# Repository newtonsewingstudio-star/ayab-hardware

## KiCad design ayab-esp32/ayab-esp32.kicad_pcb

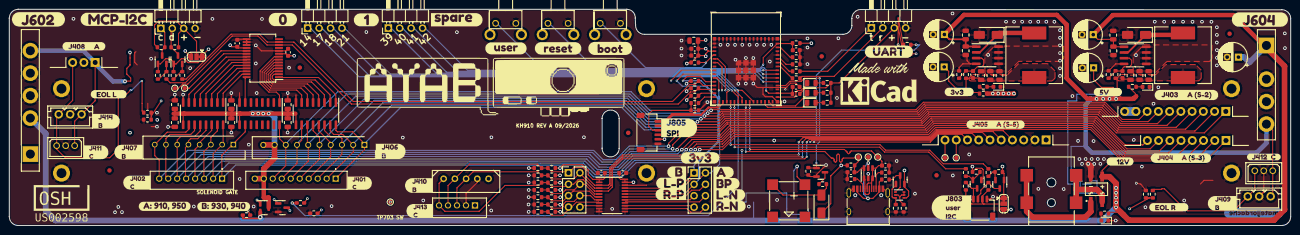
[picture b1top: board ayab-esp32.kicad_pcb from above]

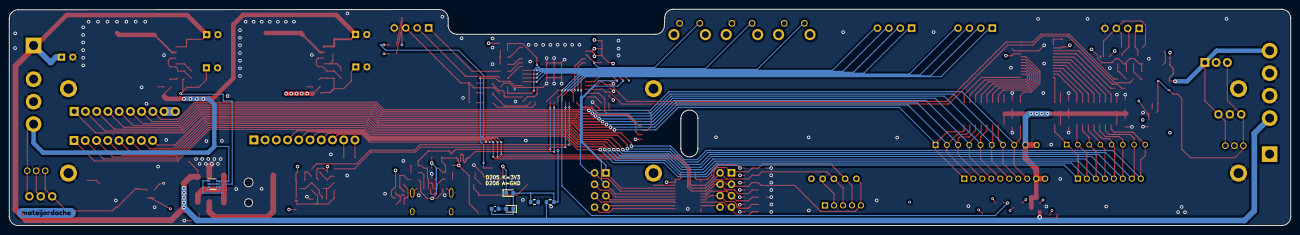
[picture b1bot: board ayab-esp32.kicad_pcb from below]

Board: 4 copper layers, 285.1 x 48.1 mm, 235 parts (7 on the bottom side), 128 nets.

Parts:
BUZZER201: MLT-8530; BUZ-SMD_4P-L8.5-W8.5-P8.50-BR
C201, C202, C203, C204, C206, C301, C305, C701, C702: 100n; C_0603_1608Metric
C205, C302, C303, C304, C601, C602, C603, C604, C605, C610, C611, C616, C617, C618, C619, C620, C621: 10u; C_0805_2012Metric
C501, C502: 47p; C_0603_1608Metric
C606, C607, C609, C612, C613: 220u; CP_Radial_D6.3mm_P2.50mm
C614, C615: 3n3; C_0603_1608Metric
D201: LED_YEL; D_0805_2012Metric
D202: LED_GRN; D_0805_2012Metric
D203: LED_RED; D_0805_2012Metric
D204, D605, D606: SS54; D_SMA
D205, D206: CDBU0130-HF; D_0603_1608Metric
D601: KMB14F; MBF-SMD_L4.8-W3.8-P2.54-LS6.8-TL
D602: 12VOK; D_0603_1608Metric
D603: 5VOK; D_0603_1608Metric
D604: 3V3OK; D_0603_1608Metric
FID101, FID102, FID103, FID104, FID105, FID106: Fiducial; Fiducial_1mm_Mask2mm
H101, H102, H103, H104, H106, H108: M2; MountingHole_2.2mm_M2_DIN965_Pad
J201: SPARE1; PinHeader_1x04_P2.54mm_Horizontal
J202: SPARE0; PinHeader_1x04_P2.54mm_Horizontal
J401: 900.965.CK35 SOLENOIDS A; 530141010
J402: 900.965.CK35 SOLENOIDS B; 530140810
J403: 910.950 SOLENOIDS A; HNC2-2.5P-10DS
J404: 910.950 SOLENOIDS B; HNC2-2.5P-8DS
J405: 910.950 ENCODERS EOL R; HNC2-2.5P-10DS
J406: 930.940 SOLENOIDS A; SHDR10W70P0X250_1X10_2740X490X590P
J407: 930.940 SOLENOIDS B; SHDR8W65P0X250_1X8_2240X490X610P
J408: 910.950 EOL L; HNC2-2.5P-3DS
J409: 930.940 EOL R; CONN-TH_3P-P2.50_X2564WV-03-N0SN
J410: 930.940 ENCODERS; CONN-TH_X2564WV-05-N0SN
J411: 900.965 EOL L; CONN-TH_3P-P2.00_A2004WV-3P
J412: 900.965 EOL R; CONN-TH_3P-P2.00_A2004WV-3P
J413: 900.965 ENCODERS; 530140510
J414: 930.940 EOL L; CONN-TH_3P-P2.50_X2564WV-03-N0SN
J501: USB_C_Receptacle_USB2.0; USB_C_Receptacle_HRO_TYPE-C-31-M-12
J601: VIN; DC-IN-TH_DC-005-5A-2.0-SMT
J602: Brother_5P
J604: Brother_4R; Brother_4P
J701: CTRL_3v3; PinHeader_2x04_P2.54mm_Vertical
J702: CTRL_5V; PinHeader_2x04_P2.54mm_Vertical
J801: AYAB_UART; PinHeader_1x04_P2.54mm_Horizontal
J802, J804: I2C_VBUS; SolderJumper-3_P1.3mm_Bridged12_RoundedPad1.0x1.5mm
J803: USER_I2C; JST_SH_SM04B-SRSS-TB_1x04-1MP_P1.00mm_Horizontal
J805: AYAB_SPI; JST_SH_SM06B-SRSS-TB_1x06-1MP_P1.00mm_Horizontal
J806: AYAB_I2C; PinHeader_1x04_P2.54mm_Horizontal
L601, L602: 47uH; L_12x12mm_H8mm
Q201, Q801, Q802, Q803, Q804, Q806: AO3400A; SOT-23
Q501: BCM857BV; SOT-363_SC-70-6
Q502, Q805: LP9435LT1G; SOT-23
R101, R102, R202, R203, R204, R209, R210, R604, R803, R804, R807, R808, R811, R812, R816, R817: 5k1; R_0603_1608Metric
R201, R205, R206, R207, R208, R211, R213, R214, R216, R603, R701, R702, R703, R704, R705, R706, R707, R708, R709, R710, R711, R712, R713, R714, R735, R736, R737, R738, R814, R815, R821: 10k; R_0603_1608Metric
R212, R504, R610: 0R; R_0603_1608Metric
R215: 47k; R_0603_1608Metric
R501: 1k5; R_0603_1608Metric
R502, R820, R822: 100k; R_0603_1608Metric
R503: 68k; R_0603_1608Metric
R605, R608: 3k3; R_0603_1608Metric
R606, R607: 1k; R_0603_1608Metric
R609: 1k8; R_0603_1608Metric
R801, R802, R809, R810, R813, R818, R819: 47R; R_0603_1608Metric
SW201: USER; KEY-TH_4P-L7.5-W11.5-P4.5
SW202: RESET; KEY-TH_4P-L7.5-W11.5-P4.5
SW203: BOOTSEL; KEY-TH_4P-L7.5-W11.5-P4.5
TP301: MCP_INTA; TestPoint_Pad_D1.0mm
TP302: MCP_INTB; TestPoint_Pad_D1.0mm
TP401: 9; TestPoint_Pad_D1.0mm
TP402: 10; TestPoint_Pad_D1.0mm
TP501: USB_BUSV; TestPoint_Pad_D1.0mm
TP502: USBM; TestPoint_Pad_D1.0mm
TP503: USBP; TestPoint_Pad_D1.0mm
TP601: 12V; TestPoint_Pad_D1.0mm
TP602: 5V; TestPoint_Pad_D1.0mm
TP603: 3V3; TestPoint_Pad_D1.0mm
TP701: HALL-L-RAW; TestPoint_Pad_D1.0mm
TP702: HALL-R-RAW; TestPoint_Pad_D1.0mm
TP703: SOL12_SW; TestPoint_Pad_D1.0mm
U201: ESP32-S3-MINI-1
U301: MCP23017_SS; SSOP-28_5.3x10.2mm_P0.65mm
U302, U303, U304: ULN2003A; SOIC-16_3.9x9.9mm_P1.27mm
U403: LM66100DCKR; SOT-363_SC-70-6
U501: SRV05-4; SOT-23-6
U601, U602: XL1509; SOIC-8_3.9x4.9mm_P1.27mm
U701: SN74LVC4245; TSSOP-24_4.4x7.8mm_P0.65mm
kibuzzard-64F68412: G***; kibuzzard-64F68412
kibuzzard-65A1AC88: G***; kibuzzard-65A1AC88
kibuzzard-65A1ADEE: G***; kibuzzard-65A1ADEE
kibuzzard-65A1DFCB: G***; kibuzzard-65A1DFCB
kibuzzard-65A2E0AA: G***; kibuzzard-65A2E0AA
kibuzzard-65A2E6F1: G***; kibuzzard-65A2E6F1
kibuzzard-65A2E096: G***; kibuzzard-65A2E096
kibuzzard-65A40139: G***; kibuzzard-65A40139
kibuzzard-65BC6282: G***; kibuzzard-65BC6282
kibuzzard-65BFAF9E: G***; kibuzzard-65BFAF9E
kibuzzard-65BFB941: G***; kibuzzard-65BFB941
kibuzzard-65BFD8A4: G***; kibuzzard-65BFD8A4
kibuzzard-65BFD8C0: G***; kibuzzard-65BFD8C0
kibuzzard-65BFD8D6: G***; kibuzzard-65BFD8D6
kibuzzard-65BFD8DF: G***; kibuzzard-65BFD8DF
kibuzzard-65BFD8F7: G***; kibuzzard-65BFD8F7
kibuzzard-65BFD82E: G***; kibuzzard-65BFD82E
kibuzzard-65BFD84C: G***; kibuzzard-65BFD84C
kibuzzard-65BFD746: G***; kibuzzard-65BFD746
kibuzzard-65BFD822: G***; kibuzzard-65BFD822
kibuzzard-65BFD836: G***; kibuzzard-65BFD836
kibuzzard-65BFD865: G***; kibuzzard-65BFD865
kibuzzard-65BFD887: G***; kibuzzard-65BFD887
kibuzzard-65BFD893: G***; kibuzzard-65BFD893
kibuzzard-65BFD905: G***; kibuzzard-65BFD905
kibuzzard-65BFE03F: G***; kibuzzard-65BFE03F
kibuzzard-65BFE052: G***; kibuzzard-65BFE052
kibuzzard-65C3D944: G***; kibuzzard-65C3D944
kibuzzard-65C3E68A: G***; kibuzzard-65C3E68A
kibuzzard-659A3543: G***; kibuzzard-659A3543
kibuzzard-659F41CB: G***; kibuzzard-659F41CB
kibuzzard-659F49E4: G***; kibuzzard-659F49E4
kibuzzard-659F49F4: G***; kibuzzard-659F49F4
kibuzzard-65834FF6: G***; kibuzzard-65834FF6
kibuzzard-658236A5: G***; kibuzzard-658236A5
kibuzzard-658236BF: G***; kibuzzard-658236BF
kibuzzard-658236C5: G***; kibuzzard-658236C5
kibuzzard-658236E5: G***; kibuzzard-658236E5
kibuzzard-658236F2: G***; kibuzzard-658236F2
kibuzzard-658236FD: G***; kibuzzard-658236FD
kibuzzard-6583500B: G***; kibuzzard-6583500B
kibuzzard-65823743: G***; kibuzzard-65823743

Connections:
+3V3: BUZZER201.1 (+), C203.1, C204.1, C205.1, C301.1, C305.1, C701.1, D204.1 (K), D205.1 (K), J801.3, J802.1, J804.1, J805.5, Q801.1 (G), Q802.1 (G), Q803.1 (G), Q804.1 (G), R201.1, R202.1, R203.1, R204.1, R205.1, R206.1, R209.1, R210.1, R213.1, R214.1, R501.1, R605.1, R610.2, R803.1, R804.1, R811.1, R812.1, R814.1, U201.3 (3V3), U301.9 (VDD), U301.18 (~RESET), U701.23 (3V3), U701.24 (3V3)
+5V: C602.1, C609.1, C611.1, C702.1, J405.1, J408.1, J409.1, J410.1, J411.1, J412.1, J413.1, J414.1, J602.5, J604.4, J802.3, J804.3, Q501.4 (E2), Q502.2 (S), R604.1, R702.1, R704.1, R706.1, R708.1, R710.1, R712.1, R714.1, U403.3 (C2), U403.6 (C1), U602.1 (VIN), U701.1 (5V), U701.2 (DIR)
+12V: C601.1, C606.1, C607.1, C610.1, D601.3 (+), J602.2, J604.1, Q805.2 (S), R215.1, R603.1, R820.1, TP601.1, U601.1 (VIN)
/AUX-CONNECTORS/AUX_SCL: J803.1, Q801.3 (D), R807.2
/AUX-CONNECTORS/AUX_SDA: J803.2, Q802.3 (D), R808.2
/AUX-CONNECTORS/AYAB_CIPO: R813.1, U201.15 (GPIO11/TOUCH11/ADC2_CH0/FSPID/FSPIIO5/S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)
/AUX-CONNECTORS/AYAB_COPI: J805.2, U201.16 (GPIO12/TOUCH12/ADC2_CH1/FSPICLK/FSPIIO6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)
/AUX-CONNECTORS/AYAB_CS: J805.1, R814.2, U201.14 (GPIO10/TOUCH10/ADC1_CH9/FSPICS0/FSPIIO4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)
/AUX-CONNECTORS/AYAB_RX: J801.1, R818.2
/AUX-CONNECTORS/AYAB_SCK: J805.4, U201.17 (GPIO13/TOUCH13/ADC2_CH2/FSPIQ/FSPIIO7/S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)
/AUX-CONNECTORS/AYAB_SCL: R209.2, R809.1, U201.13 (GPIO9/TOUCH9/ADC1_CH8/FSPIHD/SUBSPIHD), U301.12 (SCK)
/AUX-CONNECTORS/AYAB_SDA: R210.2, R810.1, U201.12 (GPIO8/TOUCH8/ADC1_CH7/SUBSPICS1), U301.13 (SDA)
/AUX-CONNECTORS/AYAB_TX: J801.2, R819.1
/AUX-CONNECTORS/CIPO: J805.3, R813.2, R815.1
/AUX-CONNECTORS/I2C_SCL: R801.1, U201.20 (GPIO16/U0CTS/ADC2_CH5/XTAL_32K_N)
/AUX-CONNECTORS/I2C_SDA: R802.1, U201.19 (GPIO15/U0RTS/ADC2_CH4/XTAL_32K_P)
/AUX-CONNECTORS/I2C_VBUS: J804.2, J806.3, R816.1, R817.1
/AUX-CONNECTORS/MCP_SCL: J806.1, Q803.3 (D), R816.2
/AUX-CONNECTORS/MCP_SDA: J806.2, Q804.3 (D), R817.2
/AUX-CONNECTORS/UART_RX: R818.1, U201.40 (U0RXD/GPIO44/CLK_OUT2)
/AUX-CONNECTORS/UART_TX: R819.2, U201.39 (U0TXD/GPIO43/CLK_OUT1)
/AUX-CONNECTORS/USER_I2C_VBUS: J802.2, J803.3, R807.1, R808.1
/BROTHER-CONNECTORS/ENC_BELTPHASE: J405.6, J410.5, J413.5, J702.3, R705.1, R706.2, U701.5 (A3)
/BROTHER-CONNECTORS/ENC_V1: J405.4, J410.4, J413.4, J702.1, R701.1, R702.2, U701.3 (A1)
/BROTHER-CONNECTORS/ENC_V2: J405.5, J410.3, J413.3, J702.2, R703.1, R704.2, U701.4 (A2)
/BROTHER-CONNECTORS/EOL_L: J408.3, J411.3, J414.3, R735.1, TP701.1
/BROTHER-CONNECTORS/EOL_R: J409.3, J412.3, R737.1, TP702.1
/BROTHER-CONNECTORS/EOL_R_N: J202.2, J405.8, R213.2, U201.21 (GPIO17/U1TXD/ADC2_CH6)
/BROTHER-CONNECTORS/EOL_R_S: J202.3, J405.7, R214.2, U201.22 (GPIO18/U1RXD/ADC2_CH7/CLK_OUT3)
/BROTHER-CONNECTORS/SOL_0: J401.8, J403.8, J406.8, U303.16 (O1)
/BROTHER-CONNECTORS/SOL_1: J401.7, J403.7, J406.7, U302.10 (O7)
/BROTHER-CONNECTORS/SOL_2: J401.6, J403.6, J406.6, U302.11 (O6)
/BROTHER-CONNECTORS/SOL_3: J401.5, J403.5, J406.5, U302.12 (O5)
/BROTHER-CONNECTORS/SOL_4: J401.4, J403.4, J406.4, U302.13 (O4)
/BROTHER-CONNECTORS/SOL_5: J401.3, J403.3, J406.3, U302.14 (O3)
/BROTHER-CONNECTORS/SOL_6: J401.2, J403.2, J406.2, U302.15 (O2)
/BROTHER-CONNECTORS/SOL_7: J401.1, J403.1, J406.1, U302.16 (O1)
/BROTHER-CONNECTORS/SOL_8: J402.8, J404.8, J407.8, U304.10 (O7)
/BROTHER-CONNECTORS/SOL_9: J402.7, J404.7, J407.7, U304.11 (O6)
/BROTHER-CONNECTORS/SOL_A: J402.6, J404.6, J407.6, U304.12 (O5)
/BROTHER-CONNECTORS/SOL_B: J402.5, J404.5, J407.5, U304.13 (O4)
/BROTHER-CONNECTORS/SOL_C: J402.4, J404.4, J407.4, U304.14 (O3)
/BROTHER-CONNECTORS/SOL_D: J402.3, J404.3, J407.3, U304.15 (O2)
/BROTHER-CONNECTORS/SOL_E: J402.2, J404.2, J407.2, U304.16 (O1)
/BROTHER-CONNECTORS/SOL_F: J402.1, J404.1, J407.1, U303.10 (O7)
/ESP32/BOOT0: R206.2, SW203.1, U201.4 (GPIO0/BOOT)
/ESP32/BOOT1: R207.1, U201.44 (GPIO46)
/ESP32/BUZZER: Q201.1 (G), R211.1, U201.34 (GPIO38/FSPIWP/SUBSPIWP)
/ESP32/ENC_A: J701.1, U201.9 (GPIO5/TOUCH5/ADC1_CH4), U701.21 (B1)
/ESP32/ENC_B: J701.2, U201.10 (GPIO6/TOUCH6/ADC1_CH5), U701.20 (B2)
/ESP32/ENC_BP: J701.3, U201.11 (GPIO7/TOUCH7/ADC1_CH6), U701.19 (B3)
/ESP32/ESP40: J201.2, U201.36 (MTDO/GPIO40/CLK_OUT2)
/ESP32/ESP41: J201.3, U201.37 (MTDI/GPIO41/CLK_OUT1)
/ESP32/ESP42: J201.4, U201.38 (MTMS/GPIO42)
/ESP32/FRONT_PANEL_AUX: J202.1, U201.18 (GPIO14/TOUCH14/ADC2_CH3/FSPIWP/FSPIDQS/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)
/ESP32/GRN: D202.1 (K), U201.29 (SPIIO5/GPIO34/FSPICS0/SUBSPICS0)
/ESP32/HALL_L_ADC: R735.2, R736.1, U201.5 (GPIO1/TOUCH1/ADC1_CH0)
/ESP32/HALL_R_ADC: R737.2, R738.1, U201.6 (GPIO2/TOUCH2/ADC1_CH1)
/ESP32/MACHINE_PWR_SENSE: C206.1, D205.2 (A), D206.1 (K), R215.2, R216.1, U201.8 (GPIO4/TOUCH4/ADC1_CH3)
/ESP32/PANEL_INT: J201.1, U201.35 (MTCK/GPIO39/CLK_OUT3/SUBSPICS1)
/ESP32/RED: D203.1 (K), U201.28 (SPIIO4/GPIO33/FSPIHD/SUBSPIHD)
/ESP32/USB_M: C501.1, J501.A7 (D-), J501.B7 (D-), R501.2, TP502.1, U201.23 (GPIO19/U1RTS/ADC2_CH8/CLK_OUT2/USB_D-), U501.1 (IO1), U501.6 (IO4)
/ESP32/USB_P: C502.1, J501.A6 (D+), J501.B6 (D+), TP503.1, U201.24 (GPIO20/U1CTS/ADC2_CH9/CLK_OUT1/USB_D+), U501.3 (IO2), U501.4 (IO3)
/ESP32/USER_BUTTON: C201.1, R201.2, SW201.1, U201.32 (SPIIO7/GPIO36/FSPICLK/SUBSPICLK)
/ESP32/VCC_SPI: R208.1, U201.41 (GPIO45)
/ESP32/YEL: D201.1 (K), U201.31 (SPIIO6/GPIO35/FSPID/SUBSPID)
/ESP32/nRST: C202.1, R205.2, SW202.1, U201.45 (EN)
/PSU/3V3_SW: C613.1, C615.2, C617.1, C619.1, C621.1, L602.2, R609.2, R610.1, TP603.1
/PSU/5V_SW: C612.1, C614.2, C616.1, C618.1, C620.1, L601.2, R608.2, TP602.1, U403.1 (E1)
/PSU/INP_1: D601.1, J601.1
/PSU/INP_2: D601.2, J601.2, J601.3
/SOLENOID DRIVERS/MCU_SOL_0: U301.8 (GPB7), U303.1 (I1)
/SOLENOID DRIVERS/MCU_SOL_1: U301.7 (GPB6), U302.7 (I7)
/SOLENOID DRIVERS/MCU_SOL_2: U301.6 (GPB5), U302.6 (I6)
/SOLENOID DRIVERS/MCU_SOL_3: U301.5 (GPB4), U302.5 (I5)
/SOLENOID DRIVERS/MCU_SOL_4: U301.4 (GPB3), U302.4 (I4)
/SOLENOID DRIVERS/MCU_SOL_5: U301.3 (GPB2), U302.3 (I3)
/SOLENOID DRIVERS/MCU_SOL_6: U301.2 (GPB1), U302.2 (I2)
/SOLENOID DRIVERS/MCU_SOL_7: U301.1 (GPB0), U302.1 (I1)
/SOLENOID DRIVERS/MCU_SOL_8: U301.21 (GPA0), U304.7 (I7)
/SOLENOID DRIVERS/MCU_SOL_9: U301.22 (GPA1), U304.6 (I6)
/SOLENOID DRIVERS/MCU_SOL_A: U301.23 (GPA2), U304.5 (I5)
/SOLENOID DRIVERS/MCU_SOL_B: U301.24 (GPA3), U304.4 (I4)
/SOLENOID DRIVERS/MCU_SOL_C: U301.25 (GPA4), U304.3 (I3)
/SOLENOID DRIVERS/MCU_SOL_D: U301.26 (GPA5), U304.2 (I2)
/SOLENOID DRIVERS/MCU_SOL_E: U301.27 (GPA6), U304.1 (I1)
/SOLENOID DRIVERS/MCU_SOL_F: U301.28 (GPA7), U303.7 (I7)
/USB/UCPD_CC1: J501.A5 (CC1), R101.1
/USB/UCPD_CC2: J501.B5 (CC2), R102.1
/USB/USB_VBUS: J501.A4 (VBUS), J501.A9 (VBUS), J501.B4 (VBUS), J501.B9 (VBUS), R504.1, TP501.1, U501.5 (VP)
GND: C201.2, C202.2, C203.2, C204.2, C205.2, C206.2, C301.2, C302.2, C303.2, C304.2, C305.2, C501.2, C502.2, C601.2, C602.2, C603.2, C604.2, C605.2, C606.2, C607.2, C609.2, C610.2, C611.2, C612.2, C613.2, C616.2, C617.2, C618.2, C619.2, C620.2, C621.2, C701.2, C702.2, D206.2 (A), D601.4 (-), D602.1 (K), D603.1 (K), D604.1 (K), D605.2 (A), D606.2 (A), H101.1, H102.1, H103.1, H104.1, H106.1, H108.1, J405.2, J408.2, J409.2, J410.2, J411.2, J412.2, J413.2, J414.2, J501.A1 (GND), J501.A12 (GND), J501.B1 (GND), J501.B12 (GND), J501.S1 (SHIELD), J602.3, J602.4, J604.2, J604.3, J801.4, J803.4, J805.6, J806.4, Q201.2 (S), Q806.2 (S), R101.2, R102.2, R207.2, R208.2, R211.2, R216.2, R502.2, R503.2, R606.2, R607.2, R701.2, R703.2, R705.2, R707.2, R709.2, R711.2, R713.2, R736.2, R738.2, R815.2, R822.1, SW201.2, SW202.2, SW203.2, U201.1 (GND), U201.2 (GND), U201.42 (GND), U201.43 (GND), U201.46 (GND), U201.47 (GND), U201.48 (GND), U201.49 (GND), U201.50 (GND), U201.51 (GND), U201.52 (GND), U201.53 (GND), U201.54 (GND), U201.55 (GND), U201.56 (GND), U201.57 (GND), U201.58 (GND), U201.59 (GND), U201.60 (GND), U201.61 (GND), U201.62 (GND), U201.63 (GND), U201.64 (GND), U201.65 (GND), U301.10 (VSS), U301.15 (A0), U301.16 (A1), U301.17 (A2), U302.8 (GND), U303.8 (GND), U304.8 (GND), U403.2 (B1), U403.5 (B2), U501.2 (VN), U601.4 (EN), U601.5 (GND), U601.6 (GND), U601.7 (GND), U601.8 (GND), U602.4 (EN), U602.5 (GND), U602.6 (GND), U602.7 (GND), U602.8 (GND), U701.11 (GND), U701.12 (GND), U701.13 (GND), U701.22 (~OE)
unnamed: D201.2 (A), R202.2
unnamed: D202.2 (A), R203.2
unnamed: D203.2 (A), R204.2
unnamed: BUZZER201.2, D204.2 (A), R212.1
unnamed: D602.2 (A), R603.2
unnamed: D603.2 (A), R604.2
unnamed: D604.2 (A), R605.2
unnamed: D605.1 (K), L601.1, U601.2 (VOUT)
unnamed: D606.1 (K), L602.1, U602.2 (VOUT)
unnamed: J405.9, TP401.1
unnamed: J405.10, TP402.1
unnamed: J701.4, U701.18 (B4)
unnamed: J701.5, U701.17 (B5)
unnamed: J701.6, U701.16 (B6)
unnamed: J701.7, U701.15 (B7)
unnamed: J701.8, U701.14 (B8)
unnamed: J702.4, R707.1, R708.2, U701.6 (A4)
unnamed: J702.5, R709.1, R710.2, U701.7 (A5)
unnamed: J702.6, R711.1, R712.2, U701.8 (A6)
unnamed: J702.7, R713.1, R714.2, U701.9 (A7)
unnamed: J702.8, U701.10 (A8)
unnamed: Q201.3 (D), R212.2
unnamed: Q501.2 (B1), Q501.5 (B2), Q501.6 (C1), R502.1
unnamed: Q501.1 (E1), Q502.3 (D), R504.2
unnamed: Q501.3 (C2), Q502.1 (G), R503.1
unnamed: Q801.2 (S), R801.2, R804.2
unnamed: Q802.2 (S), R802.2, R803.2
unnamed: Q803.2 (S), R809.2, R812.2
unnamed: Q804.2 (S), R810.2, R811.2
unnamed: Q805.1 (G), Q806.3 (D), R820.2
unnamed: Q806.1 (G), R821.2, R822.2
unnamed: TP301.1, U301.20 (INTA)
unnamed: TP302.1, U301.19 (INTB)
unnamed: C614.1, R606.1, R608.1, U601.3 (FB)
unnamed: C615.1, R607.1, R609.1, U602.3 (FB)
SOLENOID_12V_SW: C302.1, C303.1, C304.1, C603.1, C604.1, C605.1, J401.9, J401.10, J403.9, J403.10, J406.9, J406.10, Q805.3 (D), TP703.1, U302.9 (COM), U303.9 (COM), U304.9 (COM)
SOLENOID_PWR_EN: J202.4, R821.1, U201.25 (GPIO21)

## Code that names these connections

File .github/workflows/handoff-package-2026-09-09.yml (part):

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
          Important target signals:

          - GPIO1: `HALL_L_ADC`
          - GPIO2: `HALL_R_ADC`
          - GPIO4: `MACHINE_PWR_SENSE`
          - GPIO5/6/7: encoder A/B/C
          - GPIO8/9: internal I2C / MCP23017
          - GPIO10-13: display SPI
          - GPIO15/16: external/front-panel I2C
          - GPIO17: `KH910_R_K`
          - GPIO18: `KH910_R_L`
          - GPIO19/20: native USB D-/D+
          - GPIO21: `SOLENOID_PWR_EN`
          - GPIO38: buzzer
          - GPIO43/44: UART

          Native USB was re-audited carefully after an early coordinate-audit mistake. The original board's USB mapping on GPIO19/20 was already correct. The audit tooling was fixed; do not repeat the erroneous USB reroute.

          ### Machine-power sense

          GPIO4 `MACHINE_PWR_SENSE` is implemented and validated using a 47 kOhm / 10 kOhm divider from raw +12 V. This provides about 2.1 V at 12 V and useful headroom.

          ### USB / 5 V reverse-current isolation

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
          Hardware-default-OFF solenoid-power gating is implemented in the schematic.

          - GPIO21 = `SOLENOID_PWR_EN`.
          - High-side switch uses LP9435LT1G P-channel MOSFET.
          - AO3400A N-channel MOSFET pulls the P-MOS gate down when enabled.
          - Q806 source/drain orientation was specifically corrected after a body-diode safety review.
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
          - KH-910 right K and L are separate digital signals. Do not OR them.
          - Preserve native machine polarity in hardware; firmware interprets it.
          - K -> dedicated GPIO17 with external 10 kOhm pull-up to 3.3 V.
          - L -> dedicated GPIO18 with external 10 kOhm pull-up to 3.3 V.
          - Analog Hall machines use passive ADC divider paths instead of LM393 normalization.
          - Left analog Hall -> GPIO1 ADC.
          - Right analog Hall -> GPIO2 ADC.
          - Passive Hall dividers are 10 kOhm / 10 kOhm.

          ### Comparator removal
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          - J405 pad 8 currently uses legacy `/BROTHER-CONNECTORS/EOL_R_N`.
          - J405 pad 7 currently uses legacy `/BROTHER-CONNECTORS/EOL_R_S`.
          - J702 pads 6/7 currently share those legacy nets.
          - U201 GPIO17 physical pad is module pad 21 and is currently `/ESP32/ESP17`.
          - U201 GPIO18 physical pad is module pad 22 and is currently `/ESP32/ESP18`.
          - The validated schematic separates the actual KH-910 machine K/L lines from the retained U701/J702 level-shifter channels.

          ### Intended K/L PCB result

          1. Keep the actual KH-910 machine signals separate from the retained U701/J702 local channels.
          2. J405 machine K/L pins must become the dedicated KH910 machine nets.
          3. Route machine K/L to GPIO17/GPIO18.
          4. Add R213/R214 10 kOhm pull-ups to 3.3 V.
          5. Preserve the U701/J702 channels on their own valid local nets; do not accidentally merge them back into machine K/L.
          6. Use the same staged/fail-closed method as Hall: baseline PCB DRC 0/0 -> staged edit -> zone refill -> staged DRC 0/0 -> repository-path DRC 0/0 -> commit only then.
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
          Firmware has not yet been reconciled to all Rev A names/features. Experimental ESP32 firmware still contains comparator-era EOL naming in places. Later tasks include:

          - update board pin names for HALL_L_ADC / HALL_R_ADC / KH910_R_K / KH910_R_L / MACHINE_PWR_SENSE / SOLENOID_PWR_EN;
          - make GPIO21 default LOW before any solenoid logic;
          - safe startup/reset behavior;
          - diagnostic firmware for MCP23017, encoder, K/L transitions, Hall ADC values, power sense and individual safe solenoid tests;
          - local display/keypad diagnostics.
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          4. Inspect the successful K/L compiled-netlist workflow run 34377939107 if needed.
          5. Build the K/L PCB migration from current Hall-clean board state.
          6. Add R213/R214 and split machine K/L from U701/J702 local channels correctly.
          7. Route K/L to GPIO17/GPIO18 using board-aware geometry.
          8. Refill zones.
          9. Require staged and repository-path PCB DRC = 0 violations / 0 unconnected.
          10. Commit only after that gate passes.
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
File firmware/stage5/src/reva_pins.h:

#pragma once
// Derived from newtonsewingstudio-star/ayab-hardware commit ae8f7eb,
// ayab-esp32/mcu.kicad_sch. Names describe electrical nets, not polarities.
namespace reva {
constexpr int HALL_L_ADC=1, HALL_R_ADC=2, MACHINE_PWR_SENSE=4;
constexpr int ENC_A=5, ENC_B=6, ENC_BP=7;
constexpr int I2C0_SDA=8, I2C0_SCL=9;
constexpr int DISPLAY_CS=10, SPI0_CIPO=11, SPI0_COPI=12, SPI0_SCK=13;
constexpr int FRONT_PANEL_AUX=14, I2C1_SDA=15, I2C1_SCL=16;
constexpr int KH910_R_K=17, KH910_R_L=18;
constexpr int USB_D_MINUS=19, USB_D_PLUS=20;
constexpr int LED_RED=33, LED_GREEN=34, LED_YELLOW=35;
constexpr int USER_BUTTON=36, BUZZER=38, PANEL_INT=39;
constexpr int UART_TX=43, UART_RX=44, BOOT0=0, BOOT1=46;
// ESP40, ESP41, ESP42 are schematic net labels on GPIO 40,41,42.
constexpr int ESP40=40, ESP41=41, ESP42=42;
// GPIOs with no direct named net found: 3,21,26,37,47,48.
}
